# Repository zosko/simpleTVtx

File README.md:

# simpleTVtx
Making the simplest TV Transmitter

## BOM
- 2 x 0.01uF
- 1 x 10pF
- 1 x 100uF
- 1 x 10pF (trimmer)
- 1 x 10k
- 1 x 27k
- 1 x 500ohm (trimmer)
- 1 x 2SC1047 (NPN)(ECB)

## Scheme

## Board

## PCB Design

For PCB design i will use services from SeeedFusion. 

Seeed Fusion PCB Assembly Service offers one-stop prototyping for PCB manufacture, PCB assembly and as a result they produce superior quality PCBs and Fast Turnkey PCBA from 7 working days. When you prototype with Seeed Fusion, they can definitely provide Free DFA and Free functional tests for you! 

Check out their website to know about their manufacturing capabilities and service.
https://www.seeedstudio.com/prototype-pcb-assembly.html 

## Reasons to choose Seeed Studio
- They provide PCB services at extremely low pricing and with excellent quality.
- Their offer is structured in such a way that everyone may have these boards at a reasonable price.
- They have a highly knowledgeable crew that leads their clients to avail deals and guides them about the costs and rates of different services.
- A four-layer board with a comparable feature costs $5 for 10 pieces and is made in four days.
- SMT stencil with size (10cm x 13cm) is available for $8.00 per piece.

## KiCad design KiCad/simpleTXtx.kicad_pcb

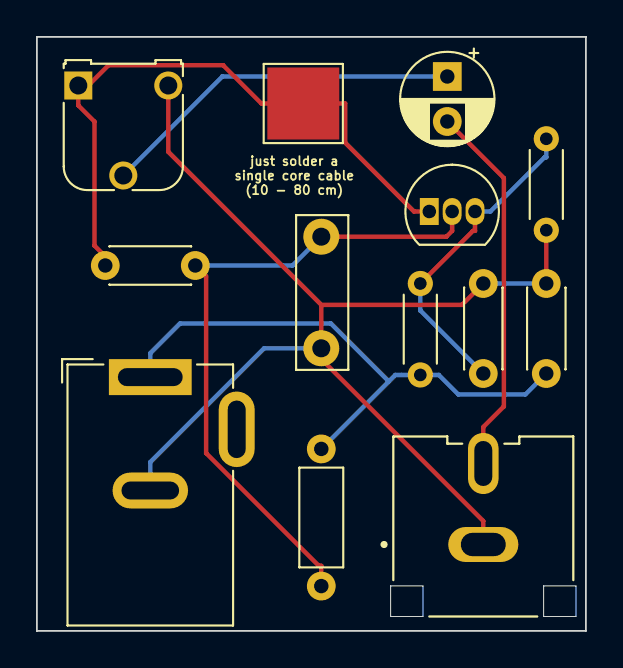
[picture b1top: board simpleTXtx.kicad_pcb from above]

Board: 2 copper layers, 30.5 x 33.0 mm, 13 parts (0 on the bottom side), 7 nets.

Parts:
AE1: Antenna; TestPoint_Pad_4.0x4.0mm
C1, C2: 0.01uF; C_Disc_D4.3mm_W1.9mm_P5.00mm
C3: 10pF; C_Disc_D11.0mm_W5.0mm_P5.00mm
C5: 100uF; CP_Radial_D5.0mm_P2.50mm
C6: 10pF; C_Disc_D4.3mm_W1.9mm_P5.00mm
J2: power; BarrelJack_GCT_DCJ200-10-A_Horizontal
J3: RCJ-044; CUI_RCJ-044
L1: L; L_Axial_L5.3mm_D2.2mm_P7.62mm_Horizontal_Vishay_IM-1
Q1: 2SC1815; TO-92_Inline
R1: 10K; R_Axial_DIN0204_L3.6mm_D1.6mm_P5.08mm_Horizontal
R2: 27K; R_Axial_DIN0204_L3.6mm_D1.6mm_P5.08mm_Horizontal
RV1: 500; Potentiometer_Runtron_RM-065_Vertical

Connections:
GND: C1.1, C2.1, C3.2, J2.2, J3.1, R1.1, RV1.3
unnamed: AE1.1 (A), C6.1, Q1.1 (E), RV1.1
unnamed: C1.2, J2.1, L1.1, R2.2
unnamed: C5.1, RV1.2
unnamed: C5.2, J3.2
unnamed: C2.2, Q1.3 (B), R1.2, R2.1
unnamed: C3.1, C6.2, L1.2, Q1.2 (C)

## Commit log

2024-12-19 update project
2025-01-13 remove one trimmer
